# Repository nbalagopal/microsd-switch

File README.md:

# microSD card switcher
This board was created by [Joel Fernandez](http://www.linuxinternals.org/joel/) and a link to his blog post is given below
- [MicroSD card remote switch](http://www.linuxinternals.org/blog/2014/06/04/a-microsd-card-remote-switcher/)
- [Demo Video](https://youtu.be/StpIihVQ7oM)

## Features
- Connect one microSD card to 2 computers( or boards)
- Ensures that the sd card is connected to only one computer at a time
- Remotely control the switch over USB serial connection

## Parts list
- Circuit board - Make this yourself or use a vendor like [OSHPark](https://oshpark.com/), [Pcbway](http://www.pcbway.com/) etc
- [microSD card sniffer](https://www.sparkfun.com/products/9419) (2)
- [10k Resistors](https://www.sparkfun.com/products/11508) (2)
- [1k Resistors](https://www.sparkfun.com/products/13760) (2)
- [LEDs](https://www.sparkfun.com/products/12062) (2)
- [SN74CBT3257D - 4 bit FET Mux/DeMux](http://www.mouser.com/ProductDetail/Texas-Instruments/SN74CBT3257D) (2)
- [microSD slot](https://www.sparkfun.com/products/127) (1)
- [Male headers](https://www.sparkfun.com/products/116) (2)
- [FTDI Cable](https://www.sparkfun.com/products/9717)

## Building the switch program
### Using docker
If you have docker installed, just run the commands given below to get the built executable. The built executable works on 64 bit linux only.
    
    export MY_WORKSPACE=<you git workspace>
    chmod 777 $MY_WORKSPACE                                              # Need to do this so that root user in the container 
                                                                         # can write to the folder
    docker run -v $MY_WORKSPACE/sw:/workspace nbalagopal/microsd_switch  # 'switch' will be in your workspace.

### Directly on Linux
    # Install libftdi
    apt-get update -y
    apt-get install -y libftdi-dev libftdi1 libftdi1-dev libftdipp1-2v5 libftdipp1-dev
    
    # Install pkg-config
    apt-get install -y pkg-config
    
    # Verify libftdi installation
    pkg-config --cflags libftdi
    # Output:
    #  
    
    pkg-config --libs libftdi
    # Output: 
    #   -lftdi1
    
    # Build using gcc
    gcc $(pkg-config --cflags libftdi)  -o switch  switch.c  $(pkg-config --libs libftdi)

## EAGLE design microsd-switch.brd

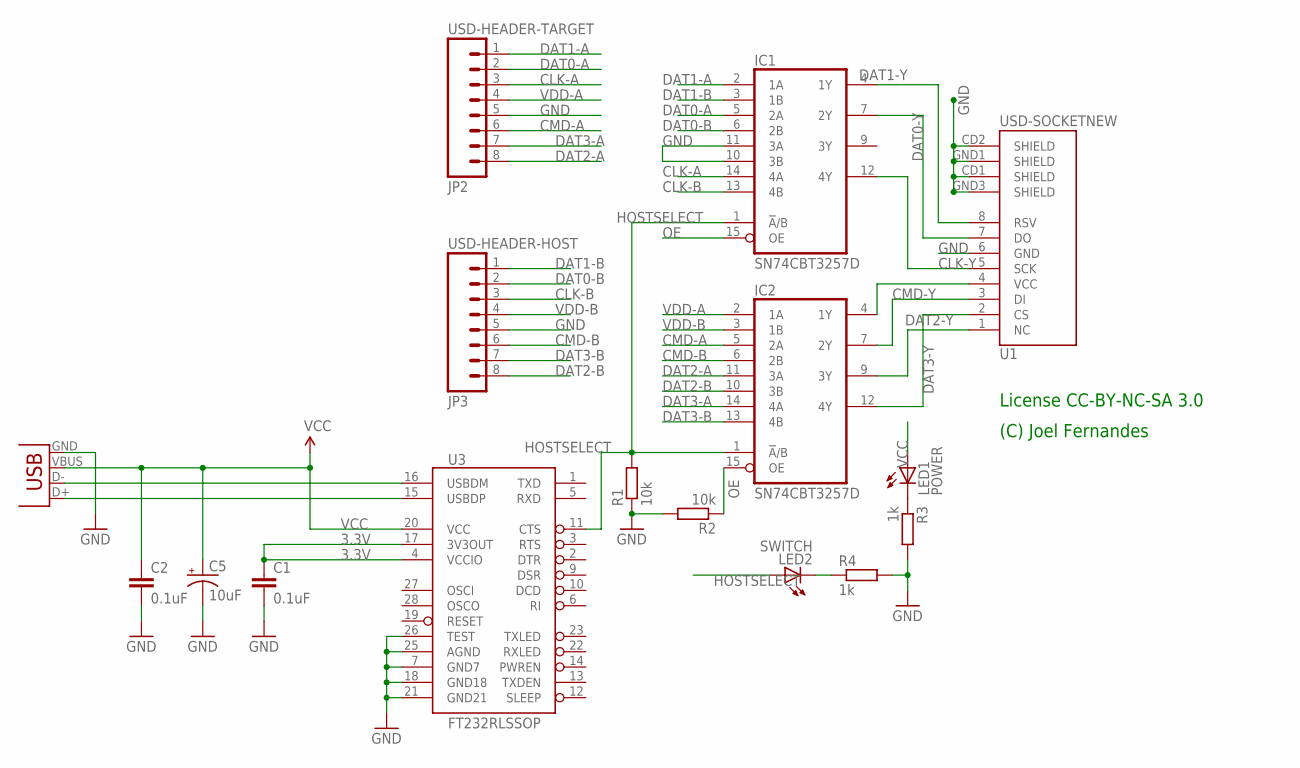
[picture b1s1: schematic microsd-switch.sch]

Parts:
C1, C2: 0.1uF; 0402-CAP
C5: 10uF; EIA3216
IC1, IC2: SN74CBT3257D; SO16
JP2: USD-HEADER-TARGET; 1X08_LOCK
JP3: USD-HEADER-HOST; 1X08_LOCK
LED1: POWER; CHIP-LED0805
LED2: SWITCH; CHIP-LED0805
R1, R2: 10k; R1206
R3, R4: 1k; R1206
U1: USD-SOCKETNEW; MICRO-SD-SOCKET-PP
U3: FT232RLSSOP; SSOP28DB
X2: USB-SMD-NS; USB-MINIB-NOSTOP

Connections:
3.3V: C1.1, U3.4 (VCCIO), U3.17 (3V3OUT)
CLK-A: IC1.14 (4A), JP2.3
CLK-B: IC1.13 (4B), JP3.3
CLK-Y: IC1.12 (4Y), U1.5 (SCK)
CMD-A: IC2.5 (2A), JP2.6
CMD-B: IC2.6 (2B), JP3.6
CMD-Y: IC2.7 (2Y), U1.3 (DI)
DAT0-A: IC1.5 (2A), JP2.2
DAT0-B: IC1.6 (2B), JP3.2
DAT0-Y: IC1.7 (2Y), U1.7 (DO)
DAT1-A: IC1.2 (1A), JP2.1
DAT1-B: IC1.3 (1B), JP3.1
DAT1-Y: IC1.4 (1Y), U1.8 (RSV)
DAT2-A: IC2.11 (3A), JP2.8
DAT2-B: IC2.10 (3B), JP3.8
DAT2-Y: IC2.9 (3Y), U1.1 (NC)
DAT3-A: IC2.14 (4A), JP2.7
DAT3-B: IC2.13 (4B), JP3.7
DAT3-Y: IC2.12 (4Y), U1.2 (CS)
GND: C1.2, C2.2, C5.C (-), IC1.8 (GND), IC1.10 (3B), IC1.11 (3A), IC2.8 (GND), JP2.5, JP3.5, R1.1, R2.2, R3.2, R4.2, U1.6 (GND), U1.CD1 (SHIELD), U1.CD2 (SHIELD), U1.GND1 (SHIELD), U1.GND3 (SHIELD), U3.7 (GND7), U3.18 (GND18), U3.21 (GND21), U3.25 (AGND), U3.26 (TEST), X2.GND
HOSTSELECT: IC1.1 (!A!/B), IC2.1 (!A!/B), LED2.A, R1.2, U3.11 (CTS)
unnamed: IC2.4 (1Y), U1.4 (VCC)
unnamed: LED1.C, R3.1
unnamed: LED2.C, R4.1
OE: IC1.15 (OE), IC2.15 (OE), R2.1
USB_D+: U3.15 (USBDP), X2.D+
USB_D-: U3.16 (USBDM), X2.D-
VCC: C2.1, C5.A (+), IC1.16 (VCC), IC2.16 (VCC), LED1.A, U3.20 (VCC), X2.VBUS
VDD-A: IC2.2 (1A), JP2.4
VDD-B: IC2.3 (1B), JP3.4

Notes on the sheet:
License CC-BY-NC-SA 3.0
(C) Joel Fernandes

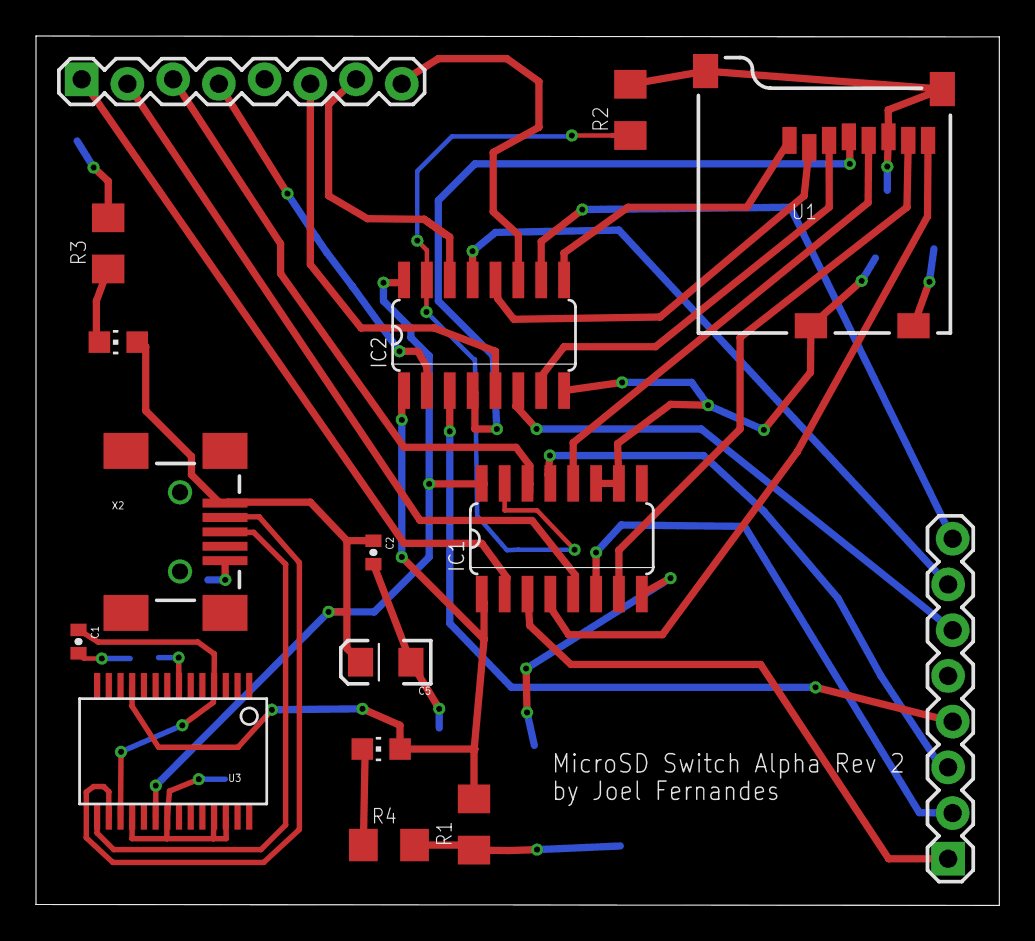
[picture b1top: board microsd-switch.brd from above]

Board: 2 copper layers, 53.5 x 48.3 mm, 16 parts (0 on the bottom side), 30 nets.

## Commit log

2014-05-13 Basic schematic for microsd switcher
2014-05-19 Update microsd-switcher project files
    Added pics, redesigned board, added a "legs" board.
2014-06-04 microsd-switch: switch: Add a program to program a board for host or target mode. Board is opened based on serial number.
2014-06-04 Add a script to simplify switching
    Usage: ./switch.sh <board-name> <on|off>
2014-06-04 update pics
2014-06-04 Add license
2014-06-04 rotate
2014-06-04 Revert "rotate"
    This reverts commit 33050dcff954b69ef18bd22d8a50f09db21a5c1d.
2014-06-04 schematic
2014-06-04 Update license
2014-06-04 schematic pdf
2014-06-05 Reduced uSD header connector size.
2014-06-05 Revert "Reduced uSD header connector size."
    This reverts commit 164ab6429ac06b889099512f0f315f421e6ea5d6.
2014-06-15 MicroSD Switch Rev Alpha released
2014-06-15 Add microsd switch project file
2014-06-15 Revert "MicroSD Switch Rev Alpha released"
    This reverts commit e0d3fcd5b1a8d34c9a3cecba9fd5e98c93932393.
2014-06-19 till handrouted neatly
2014-06-21 microsd-switch: Update board/schematic
2017-01-20 Added microSD slot, headers and and FTDI cable to parts list
2017-01-20 Add link to demo video
2017-01-29 Add build instructions
2017-01-29 Fix typo
2017-01-29 Added instructions to build using docker

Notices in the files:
parts and their libraries:
SparkFun: Licensing: CC v3.0 Share-Alike You are welcome to use this library for commercial purposes.
